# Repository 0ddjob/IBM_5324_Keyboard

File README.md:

# IBM System/23 Model 5324 Keyboard
Recreation of the keyboard for this computer to bring those without keyboards back to life.

## [Design References](/Design_Reference)

|     |Column A|Column B|Column C|Column D|Column E|Column F|Column G|Column H|Column I|Column J|Column K|
|-----|--------|--------|--------|--------|--------|--------|--------|--------|--------|--------|--------|
|Row 1| 6F/7F  | 3E     | 32     | 34     | 36     | 38     | 3A     | 3C     |        | 4B     |        |
|Row 2| 7C     | 31     | 33     | 35     | 37     |        | 39     | 3B     | 3D T   | 48     | 4C     |
|Row 3| 6D     | 20     | 22     | 24     | 26     |        | 28     | 2A     | 2C     | 47     | 49     |
|Row 4| 6C     | 54/74  | 21     | 23     | 25     | 27     | 29     | 2B     | 2D     | 44     | 4E     |
|Row 5| 6E     | 57/77  | 11     | 13     | 15     | 17     | 19     | 1B     | 59/79  | 45     | 46     |
|Row 6| 7D     | 70 T   | 12     | 14     | 16     |        | 18     | 1A     | 56/76  | 41     | 43     |
|Row 7| 71 T   | 73 T   | 0E     | 03     | 05     | 06     | 07     | 09     | 0B/7B  | 42     | 4D     |
|Row 8| 72 T   | 7E/5E  | 01     | 02     | 04     | 0F T   | 08     | 0A     | 68/78  | 40     | 4A     |

xx/yy = make/break key (send on release)<br>
T = typamatic key (repeat while held)<br>

## Keyboard Data Flow 
Refer p3-19 of the [SY34-0241-1 service manual.](/Datasheets/SY34-0241-1_IBM_5324_Computer_Service_Manual_May82_Keyboard.pdf)

The original keyboard uses a capacitive matrix where there is a capacitor for each key. When a key is pressed the capacitance increases.<br>

In my design we use standard key switches.<br>

The keyboard MCU has 11 drive lines to repeatedly scan the matrix - in my schematic these are the columns.<br>  

The increased capacitance of the active key's capacitor permits the drive-line (column) scan pulse to appear at one of the eight input lines to the sense amplifier - in my schematic these are the rows.<br>

The MCU uses the combination of the active drive line (column) and sense amplifier input line (row) to determine a scan code character (88 possible, 83 actually used).<br>

In my design the columns and rows are pulled high.  To scan the keyboard matrix we take each column low in turn.  A key press is detected when the key switch shorts the row to the column, taking the row low which is detected by the controller.  The combination of column and row is translated to a 5324 scan code and put on the bus via a buffer to ensure the 5324 accurately reads the code.<br>

An interrupt request is sent to the Model 5324 processing unit which will then read the scan code character.<br>

## Key Caps
[Key cap layout](https://gist.github.com/0ddjob/6a0642893fc0fdca74740a1e6c51e858)

|Size |Count|
|-----|-----|
|1u   |68   |
|1.25u|2    |
|1.5u |2    |
|1.75u|2    |
|2u   |6    |
|2.25u|1    |
|3u   |1    |
|9.5u |1    |
|TOTAL|83   |

|Size|Key|
|-----|---|
|1.25u|Backslash|
|1.25u|Shift LH|
|1.5u|Shift RH|
|1.5u|Field Advance|
|1.75u|Backspace|
|1.75u|Shift Lock|
|2u|Field Exit|
|2u|NP +|
|2u|NP -|
|2u|NP 0|
|2u|NP .|
|2u|Alt|
|2u|Enter (vertical)|
|3u|Field + (vertical)|
|9.5u|Space|

## [KiCad Design](/KiCad)
[Schematic](/IBM_5324_Keyboard_Schematic.pdf)

## [N-Key Rollover (NKRO) Design](/KiCad_NKRO)
Adding diodes to each key switch on their row connection.  The original keyboard doesn't have these so the modified behaviour might not be expected, thus it's "experimental".

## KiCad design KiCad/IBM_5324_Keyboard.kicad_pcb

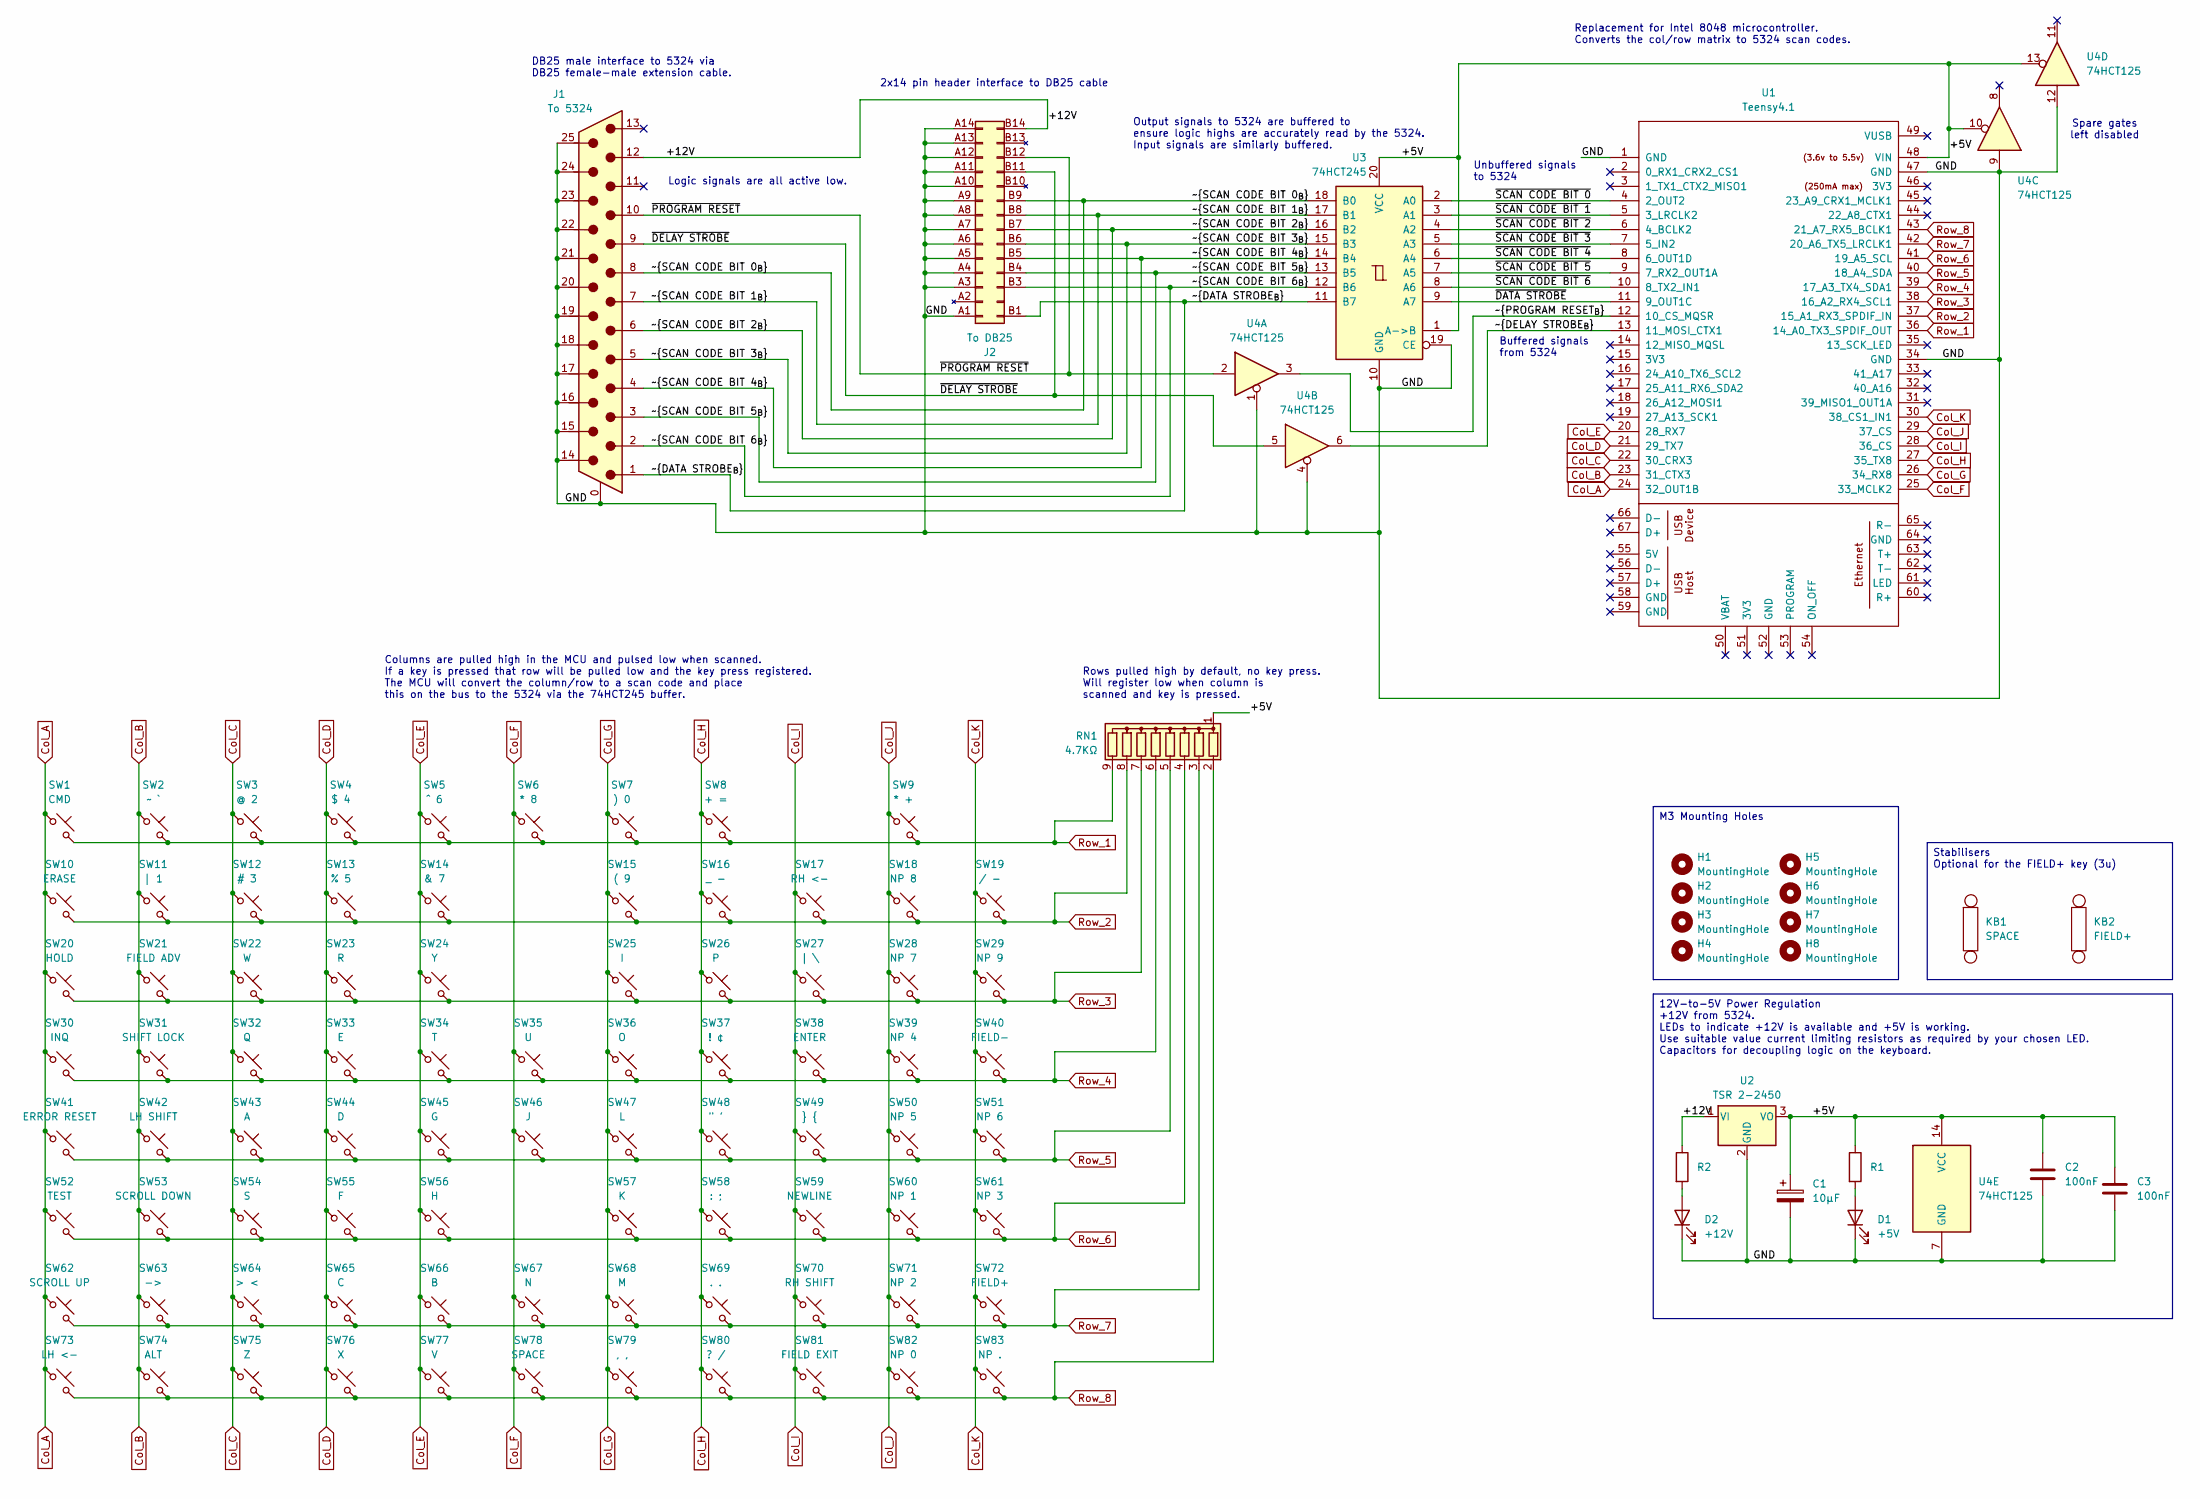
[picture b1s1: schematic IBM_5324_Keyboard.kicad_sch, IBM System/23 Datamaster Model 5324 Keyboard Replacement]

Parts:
C1: 10µF; CP_Radial_D5.0mm_P2.50mm
C2, C3: 100nF; C_Disc_D3.8mm_W2.6mm_P2.50mm
D1: +5V; LED_D5.0mm
D2: +12V; LED_D5.0mm
H1, H2, H3, H4, H5, H6, H7, H8: MountingHole; MountingHole_3.2mm_M3
J1: To 5324; L717SDB25P1ACH3R
J2: To DB25; PinHeader_2x14_P2.54mm_Vertical
KB1: SPACE; Stabilizer_Cherry_MX_8.00u
KB2: FIELD+; Stabilizer_Cherry_MX_3.00u
R1, R2: R; R_Axial_DIN0207_L6.3mm_D2.5mm_P7.62mm_Horizontal
RN1: 4.7KΩ; R_Array_SIP9
SW1: CMD; SW_Cherry_MX_PCB
SW2: ~ `; SW_Cherry_MX_PCB
SW3: @ 2; SW_Cherry_MX_PCB
SW4: $ 4; SW_Cherry_MX_PCB
SW5: ^ 6; SW_Cherry_MX_PCB
SW6: * 8; SW_Cherry_MX_PCB
SW7: ) 0; SW_Cherry_MX_PCB
SW8: + =; SW_Cherry_MX_PCB
SW9: * +; SW_Cherry_MX_PCB_1.75u
SW10: ERASE; SW_Cherry_MX_PCB
SW11: | 1; SW_Cherry_MX_PCB
SW12: # 3; SW_Cherry_MX_PCB
SW13: % 5; SW_Cherry_MX_PCB
SW14: & 7; SW_Cherry_MX_PCB
SW15: ( 9; SW_Cherry_MX_PCB
SW16: _ -; SW_Cherry_MX_PCB
SW17: RH <-; SW_Cherry_MX_PCB
SW18: NP 8; SW_Cherry_MX_PCB
SW19: / -; SW_Cherry_MX_PCB_1.75u
SW20: HOLD; SW_Cherry_MX_PCB
SW21: FIELD ADV; SW_Cherry_MX_PCB_1.50u
SW22: W; SW_Cherry_MX_PCB
SW23: R; SW_Cherry_MX_PCB
SW24: Y; SW_Cherry_MX_PCB
SW25: I; SW_Cherry_MX_PCB
SW26: P; SW_Cherry_MX_PCB
SW27: | \; SW_Cherry_MX_PCB
SW28: NP 7; SW_Cherry_MX_PCB
SW29: NP 9; SW_Cherry_MX_PCB
SW30: INQ; SW_Cherry_MX_PCB
SW31: SHIFT LOCK; SW_Cherry_MX_PCB_1.75u
SW32: Q; SW_Cherry_MX_PCB
SW33: E; SW_Cherry_MX_PCB
SW34: T; SW_Cherry_MX_PCB
SW35: U; SW_Cherry_MX_PCB
SW36: O; SW_Cherry_MX_PCB
SW37: ! ¢; SW_Cherry_MX_PCB
SW38: ENTER; SW_Cherry_MX_PCB_2.00u_90deg
SW39: NP 4; SW_Cherry_MX_PCB
SW40: FIELD-; SW_Cherry_MX_PCB
SW41: ERROR RESET; SW_Cherry_MX_PCB
SW42: LH SHIFT; SW_Cherry_MX_PCB_1.25u
SW43: A; SW_Cherry_MX_PCB
SW44: D; SW_Cherry_MX_PCB
SW45: G; SW_Cherry_MX_PCB
SW46: J; SW_Cherry_MX_PCB
SW47: L; SW_Cherry_MX_PCB
SW48: " '; SW_Cherry_MX_PCB
SW49: } {; SW_Cherry_MX_PCB
SW50: NP 5; SW_Cherry_MX_PCB
SW51: NP 6; SW_Cherry_MX_PCB
SW52: TEST; SW_Cherry_MX_PCB
SW53: SCROLL DOWN; SW_Cherry_MX_PCB
SW54: S; SW_Cherry_MX_PCB
SW55: F; SW_Cherry_MX_PCB
SW56: H; SW_Cherry_MX_PCB
SW57: K; SW_Cherry_MX_PCB
SW58: : ;; SW_Cherry_MX_PCB
SW59: NEWLINE; SW_Cherry_MX_PCB
SW60: NP 1; SW_Cherry_MX_PCB
SW61: NP 3; SW_Cherry_MX_PCB
SW62: SCROLL UP; SW_Cherry_MX_PCB
SW63: ->; SW_Cherry_MX_PCB
SW64: > <; SW_Cherry_MX_PCB_1.00u
SW65: C; SW_Cherry_MX_PCB
SW66: B; SW_Cherry_MX_PCB
SW67: N; SW_Cherry_MX_PCB
SW68: M; SW_Cherry_MX_PCB
SW69: . .; SW_Cherry_MX_PCB
SW70: RH SHIFT; SW_Cherry_MX_PCB_1.50u
SW71: NP 2; SW_Cherry_MX_PCB
SW72: FIELD+; SW_Cherry_MX_PCB_3.00u_90deg
SW73: LH <-; SW_Cherry_MX_PCB
SW74: ALT; SW_Cherry_MX_PCB_2.25u
SW75: Z; SW_Cherry_MX_PCB
SW76: X; SW_Cherry_MX_PCB
SW77: V; SW_Cherry_MX_PCB
SW78: SPACE; SW_Cherry_MX_PCB
SW79: , ,; SW_Cherry_MX_PCB
SW80: ? /; SW_Cherry_MX_PCB
SW81: FIELD EXIT; SW_Cherry_MX_PCB_2.00u
SW82: NP 0; SW_Cherry_MX_PCB_2.00u
SW83: NP .; SW_Cherry_MX_PCB_2.00u
U1: Teensy4.1; Teensy41
U2: TSR 2-2450; Converter_DCDC_TRACO_TSR2-24xxN_TSR2-24xxxN_THT
U3: 74HCT245; DIP-20_W7.62mm
U4: 74HCT125; DIP-14_W7.62mm

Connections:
/+5V: C1.1, C2.1, C3.1, R1.1, RN1.1 (common), U1.48 (VIN), U2.3 (VO), U3.1 (A->B), U3.20 (VCC), U4.10, U4.13, U4.14 (VCC)
/+12V: J1.12, J2.B14 (+12V), R2.1, U2.1 (VI)
/GND: C1.2, C2.2, C3.2, D1.1 (K), D2.1 (K), J1.0 (PAD), J1.14, J1.15, J1.16, J1.17, J1.18, J1.19, J1.20, J1.21, J1.22, J1.23, J1.24, J1.25, J2.A1 (GND), J2.A3 (GND), J2.A4 (GND), J2.A5 (GND), J2.A6 (GND), J2.A7 (GND), J2.A8 (GND), J2.A9 (GND), J2.A10 (GND), J2.A11 (GND), J2.A12 (GND), J2.A13 (GND), J2.A14 (GND), U1.1 (GND), U1.34 (GND), U1.47 (GND), U2.2 (GND), U3.10 (GND), U3.19 (CE), U4.1, U4.4, U4.7 (GND), U4.9, U4.12
/~DATA STROBE_{B}: J1.1, J2.B1 (DATA_STROBE), U3.11 (B7)
/~DATA STROBE: U1.11 (9_OUT1C), U3.9 (A7)
/~DELAY STROBE_{B}: U1.13 (11_MOSI_CTX1), U4.6
/~DELAY STROBE: J1.9, J2.B11 (DELAY_STROBE), U4.5
/~PROGRAM RESET_{B}: U1.12 (10_CS_MQSR), U4.3
/~PROGRAM RESET: J1.10, J2.B12 (PROGRAM_RESET), U4.2
/~SCAN CODE BIT 0_{B}: J1.8, J2.B9 (SCAN_CODE_BIT_0), U3.18 (B0)
/~SCAN CODE BIT 0: U1.4 (2_OUT2), U3.2 (A0)
/~SCAN CODE BIT 1_{B}: J1.7, J2.B8 (SCAN_CODE_BIT_1), U3.17 (B1)
/~SCAN CODE BIT 1: U1.5 (3_LRCLK2), U3.3 (A1)
/~SCAN CODE BIT 2_{B}: J1.6, J2.B7 (SCAN_CODE_BIT_2), U3.16 (B2)
/~SCAN CODE BIT 2: U1.6 (4_BCLK2), U3.4 (A2)
/~SCAN CODE BIT 3_{B}: J1.5, J2.B6 (SCAN_CODE_BIT_3), U3.15 (B3)
/~SCAN CODE BIT 3: U1.7 (5_IN2), U3.5 (A3)
/~SCAN CODE BIT 4_{B}: J1.4, J2.B5 (SCAN_CODE_BIT_4), U3.14 (B4)
/~SCAN CODE BIT 4: U1.8 (6_OUT1D), U3.6 (A4)
/~SCAN CODE BIT 5_{B}: J1.3, J2.B4 (SCAN_CODE_BIT_5), U3.13 (B5)
/~SCAN CODE BIT 5: U1.9 (7_RX2_OUT1A), U3.7 (A5)
/~SCAN CODE BIT 6_{B}: J1.2, J2.B3 (SCAN_CODE_BIT_6), U3.12 (B6)
/~SCAN CODE BIT 6: U1.10 (8_TX2_IN1), U3.8 (A6)
Col_A: SW1.1, SW10.1, SW20.1, SW30.1, SW41.1, SW52.1, SW62.1, SW73.1, U1.24 (32_OUT1B)
Col_B: SW2.1, SW11.1, SW21.1, SW31.1, SW42.1, SW53.1, SW63.1, SW74.1, U1.23 (31_CTX3)
Col_C: SW3.1, SW12.1, SW22.1, SW32.1, SW43.1, SW54.1, SW64.1, SW75.1, U1.22 (30_CRX3)
Col_D: SW4.1, SW13.1, SW23.1, SW33.1, SW44.1, SW55.1, SW65.1, SW76.1, U1.21 (29_TX7)
Col_E: SW5.1, SW14.1, SW24.1, SW34.1, SW45.1, SW56.1, SW66.1, SW77.1, U1.20 (28_RX7)
Col_F: SW6.1, SW35.1, SW46.1, SW67.1, SW78.1, U1.25 (33_MCLK2)
Col_G: SW7.1, SW15.1, SW25.1, SW36.1, SW47.1, SW57.1, SW68.1, SW79.1, U1.26 (34_RX8)
Col_H: SW8.1, SW16.1, SW26.1, SW37.1, SW48.1, SW58.1, SW69.1, SW80.1, U1.27 (35_TX8)
Col_I: SW17.1, SW27.1, SW38.1, SW49.1, SW59.1, SW70.1, SW81.1, U1.28 (36_CS)
Col_J: SW9.1, SW18.1, SW28.1, SW39.1, SW50.1, SW60.1, SW71.1, SW82.1, U1.29 (37_CS)
Col_K: SW19.1, SW29.1, SW40.1, SW51.1, SW61.1, SW72.1, SW83.1, U1.30 (38_CS1_IN1)
unnamed: D1.2 (A), R1.2
unnamed: D2.2 (A), R2.2
Row_1: RN1.9 (R8), SW1.2, SW2.2, SW3.2, SW4.2, SW5.2, SW6.2, SW7.2, SW8.2, SW9.2, U1.36 (14_A0_TX3_SPDIF_OUT)
Row_2: RN1.8 (R7), SW10.2, SW11.2, SW12.2, SW13.2, SW14.2, SW15.2, SW16.2, SW17.2, SW18.2, SW19.2, U1.37 (15_A1_RX3_SPDIF_IN)
Row_3: RN1.7 (R6), SW20.2, SW21.2, SW22.2, SW23.2, SW24.2, SW25.2, SW26.2, SW27.2, SW28.2, SW29.2, U1.38 (16_A2_RX4_SCL1)
Row_4: RN1.6 (R5), SW30.2, SW31.2, SW32.2, SW33.2, SW34.2, SW35.2, SW36.2, SW37.2, SW38.2, SW39.2, SW40.2, U1.39 (17_A3_TX4_SDA1)
Row_5: RN1.5 (R4), SW41.2, SW42.2, SW43.2, SW44.2, SW45.2, SW46.2, SW47.2, SW48.2, SW49.2, SW50.2, SW51.2, U1.40 (18_A4_SDA)
Row_6: RN1.4 (R3), SW52.2, SW53.2, SW54.2, SW55.2, SW56.2, SW57.2, SW58.2, SW59.2, SW60.2, SW61.2, U1.41 (19_A5_SCL)
Row_7: RN1.3 (R2), SW62.2, SW63.2, SW64.2, SW65.2, SW66.2, SW67.2, SW68.2, SW69.2, SW70.2, SW71.2, SW72.2, U1.42 (20_A6_TX5_LRCLK1)
Row_8: RN1.2 (R1), SW73.2, SW74.2, SW75.2, SW76.2, SW77.2, SW78.2, SW79.2, SW80.2, SW81.2, SW82.2, SW83.2, U1.43 (21_A7_RX5_BCLK1)

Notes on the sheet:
Columns are pulled high in the MCU and pulsed low when scanned. If a key is pressed that row will be pulled low and the key press registered. The MCU will convert the column/row to a scan code and place this on the bus to the 5324 via the 74HCT245 buffer.
Buffered signals from 5324
Spare gates left disabled
Logic signals are all active low.
2x14 pin header interface to DB25 cable
Replacement for Intel 8048 microcontroller. Converts the col/row matrix to 5324 scan codes.
DB25 male interface to 5324 via DB25 female-male extension cable.
Unbuffered signals to 5324
Output signals to 5324 are buffered to ensure logic highs are accurately read by the 5324. Input signals are similarly buffered.
Rows pulled high by default, no key press. Will register low when column is scanned and key is pressed.
M3 Mounting Holes
Stabilisers Optional for the FIELD+ key (3u)
12V-to-5V Power Regulation +12V from 5324. LEDs to indicate +12V is available and +5V is working. Use suitable value current limiting resistors as required by your chosen LED. Capacitors for decoupling logic on the keyboard.

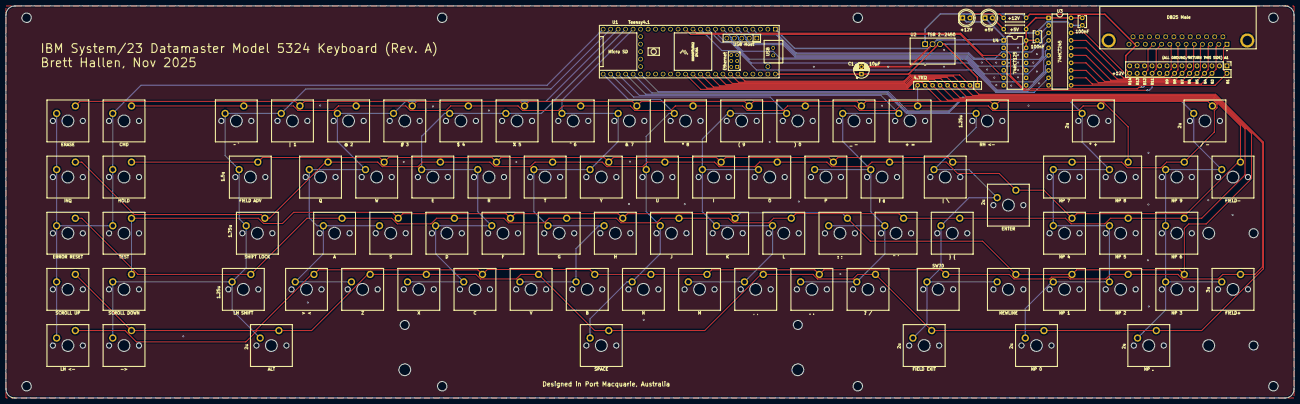
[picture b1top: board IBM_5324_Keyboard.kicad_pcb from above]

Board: 2 copper layers, 437.0 x 133.0 mm, 107 parts (0 on the bottom side), 44 nets.

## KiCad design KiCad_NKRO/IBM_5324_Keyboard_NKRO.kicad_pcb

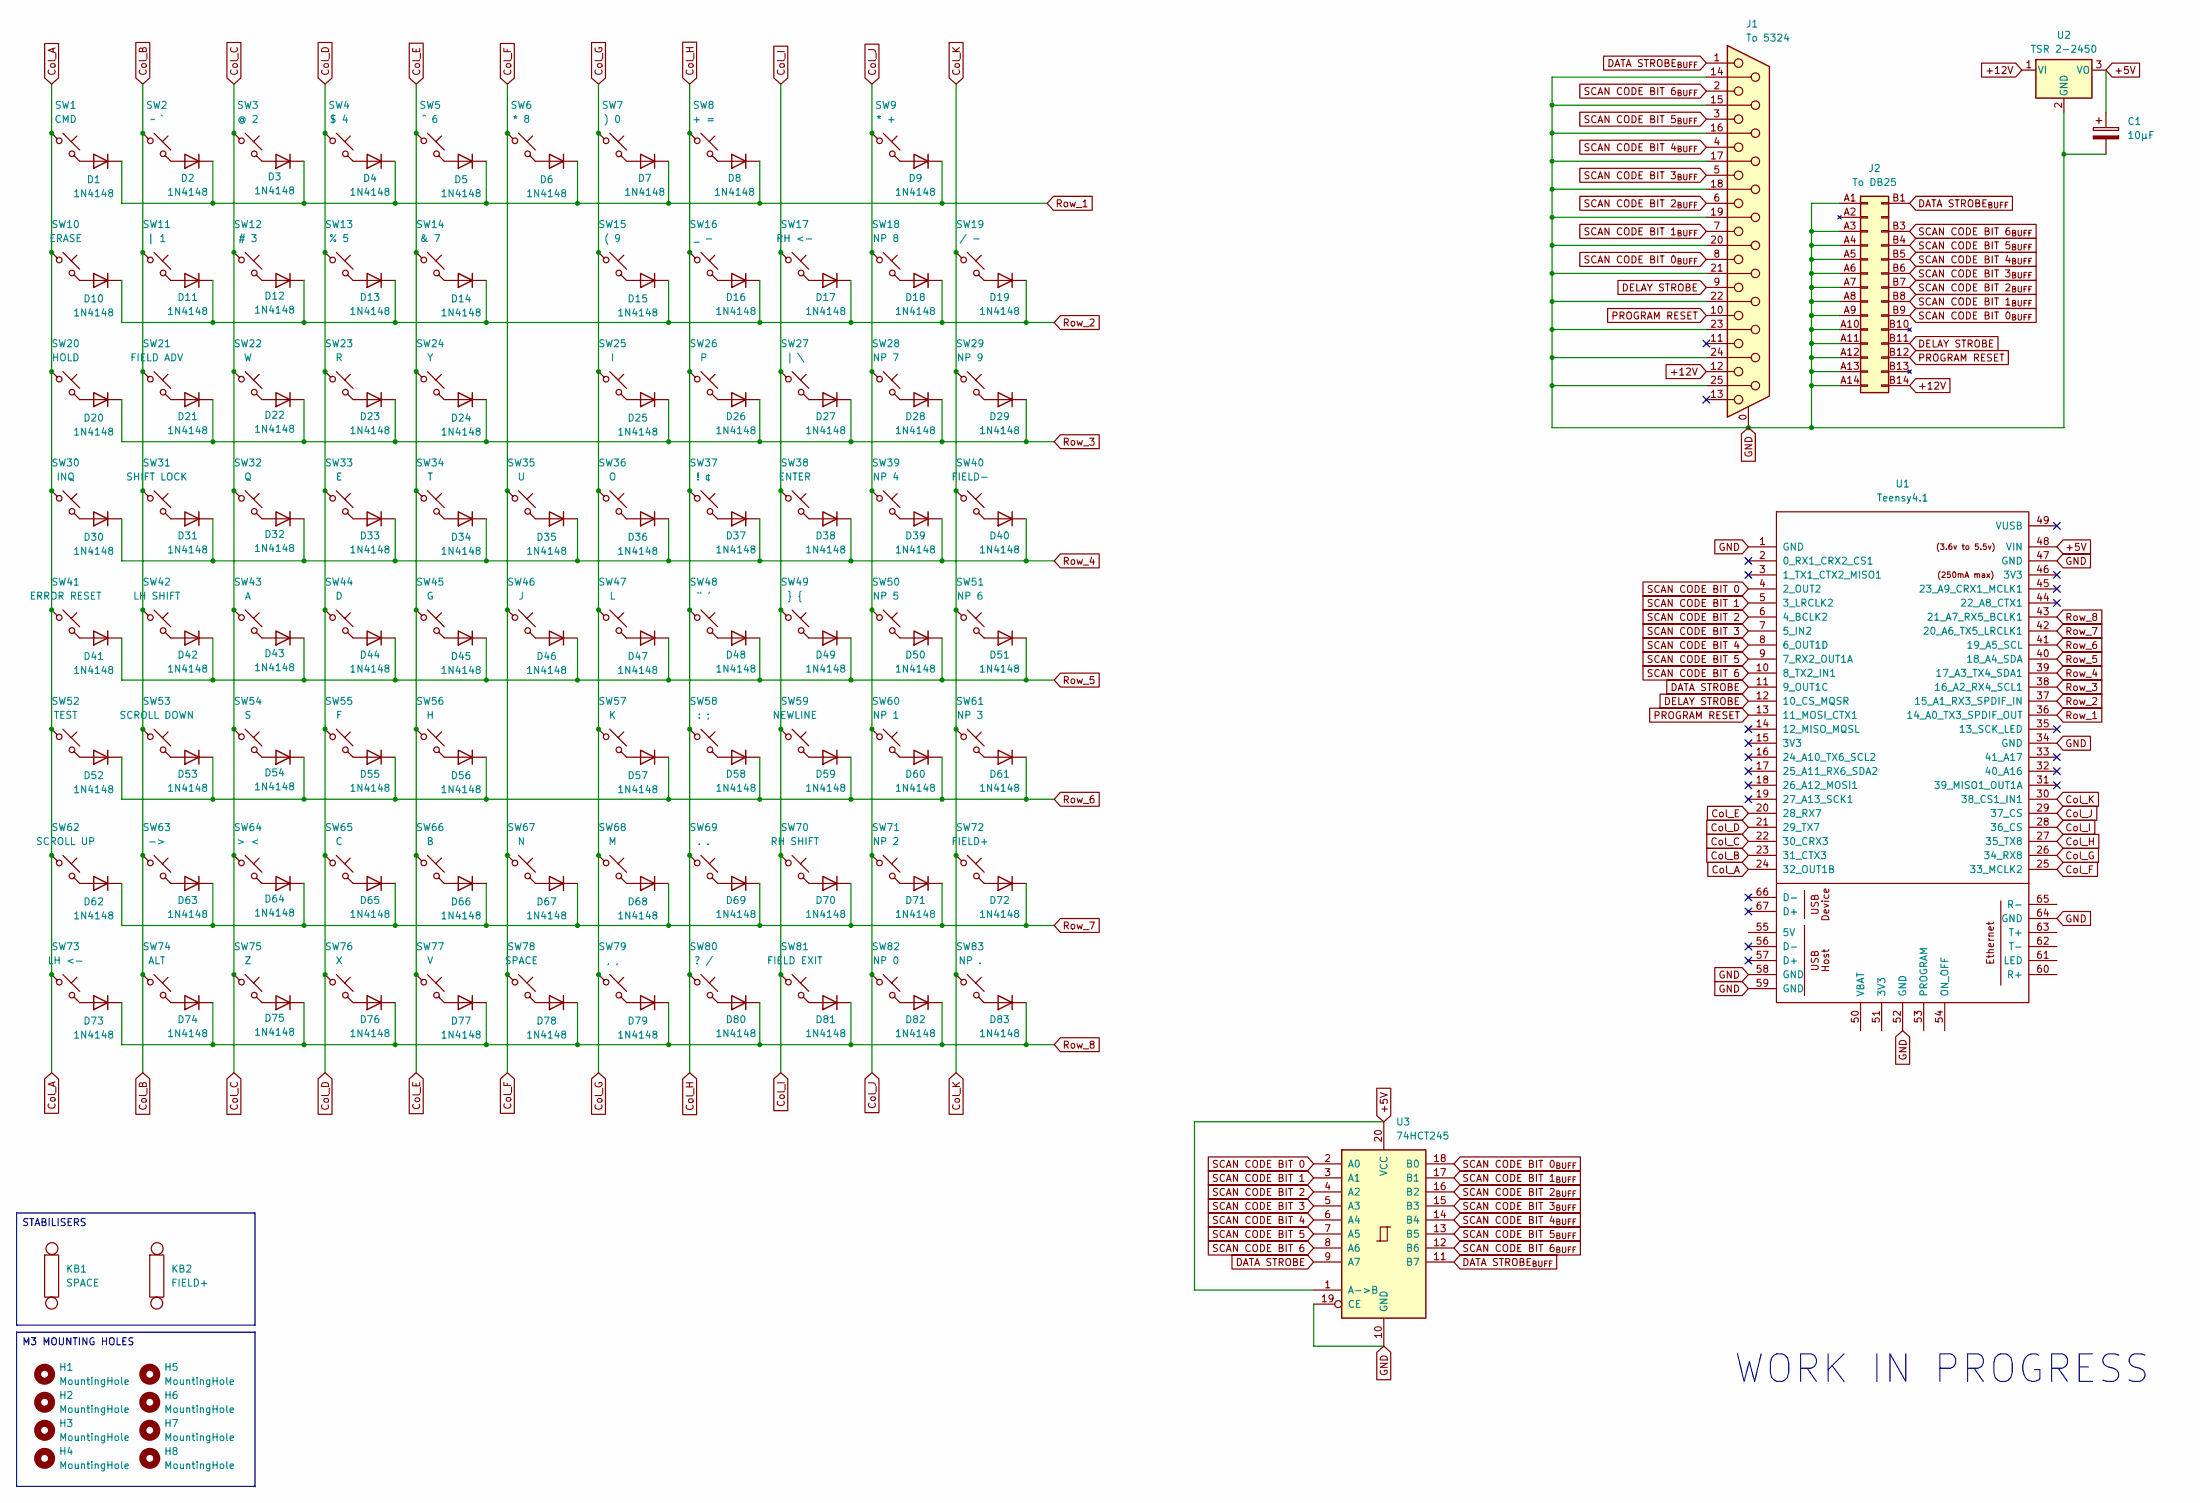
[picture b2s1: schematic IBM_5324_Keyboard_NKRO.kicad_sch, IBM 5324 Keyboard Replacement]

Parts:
C1: 10µF; CP_Radial_D5.0mm_P2.50mm
D1, D2, D3, D4, D5, D6, D7, D8, D9, D10, D11, D12, D13, D14, D15, D16, D17, D18, D19, D20, D21, D22, D23, D24, D25, D26, D27, D28, D29, D30, D31, D32, D33, D34, D35, D36, D37, D38, D39, D40, D41, D42, D43, D44, D45, D46, D47, D48, D49, D50, D51, D52, D53, D54, D55, D56, D57, D58, D59, D60, D61, D62, D63, D64, D65, D66, D67, D68, D69, D70, D71, D72, D73, D74, D75, D76, D77, D78, D79, D80, D81, D82, D83: 1N4148; D_SOD-123
H1, H2, H3, H4, H5, H6, H7, H8: MountingHole; MountingHole_3.2mm_M3
J1: To 5324; L77SDB25SA4CH4F
J2: To DB25; PinHeader_2x14_P2.54mm_Vertical
KB1: SPACE; Stabilizer_Cherry_MX_8.00u
KB2: FIELD+; Stabilizer_Cherry_MX_3.00u
SW1: CMD; SW_Cherry_MX_PCB
SW2: ~ `; SW_Cherry_MX_PCB
SW3: @ 2; SW_Cherry_MX_PCB
SW4: $ 4; SW_Cherry_MX_PCB
SW5: ^ 6; SW_Cherry_MX_PCB
SW6: * 8; SW_Cherry_MX_PCB
SW7: ) 0; SW_Cherry_MX_PCB
SW8: + =; SW_Cherry_MX_PCB
SW9: * +; SW_Cherry_MX_PCB_1.75u
SW10: ERASE; SW_Cherry_MX_PCB
SW11: | 1; SW_Cherry_MX_PCB
SW12: # 3; SW_Cherry_MX_PCB
SW13: % 5; SW_Cherry_MX_PCB
SW14: & 7; SW_Cherry_MX_PCB
SW15: ( 9; SW_Cherry_MX_PCB
SW16: _ -; SW_Cherry_MX_PCB
SW17: RH <-; SW_Cherry_MX_PCB
SW18: NP 8; SW_Cherry_MX_PCB
SW19: / -; SW_Cherry_MX_PCB_1.75u
SW20: HOLD; SW_Cherry_MX_PCB
SW21: FIELD ADV; SW_Cherry_MX_PCB_1.50u
SW22: W; SW_Cherry_MX_PCB
SW23: R; SW_Cherry_MX_PCB
SW24: Y; SW_Cherry_MX_PCB
SW25: I; SW_Cherry_MX_PCB
SW26: P; SW_Cherry_MX_PCB
SW27: | \; SW_Cherry_MX_PCB
SW28: NP 7; SW_Cherry_MX_PCB
SW29: NP 9; SW_Cherry_MX_PCB
SW30: INQ; SW_Cherry_MX_PCB
SW31: SHIFT LOCK; SW_Cherry_MX_PCB_1.75u
SW32: Q; SW_Cherry_MX_PCB
SW33: E; SW_Cherry_MX_PCB
SW34: T; SW_Cherry_MX_PCB
SW35: U; SW_Cherry_MX_PCB
SW36: O; SW_Cherry_MX_PCB
SW37: ! ¢; SW_Cherry_MX_PCB
SW38: ENTER; SW_Cherry_MX_PCB_2.00u_90deg
SW39: NP 4; SW_Cherry_MX_PCB
SW40: FIELD-; SW_Cherry_MX_PCB
SW41: ERROR RESET; SW_Cherry_MX_PCB
SW42: LH SHIFT; SW_Cherry_MX_PCB_1.25u
SW43: A; SW_Cherry_MX_PCB
SW44: D; SW_Cherry_MX_PCB
SW45: G; SW_Cherry_MX_PCB
SW46: J; SW_Cherry_MX_PCB
SW47: L; SW_Cherry_MX_PCB
SW48: " '; SW_Cherry_MX_PCB
SW49: } {; SW_Cherry_MX_PCB
SW50: NP 5; SW_Cherry_MX_PCB
SW51: NP 6; SW_Cherry_MX_PCB
SW52: TEST; SW_Cherry_MX_PCB
SW53: SCROLL DOWN; SW_Cherry_MX_PCB
SW54: S; SW_Cherry_MX_PCB
SW55: F; SW_Cherry_MX_PCB
SW56: H; SW_Cherry_MX_PCB
SW57: K; SW_Cherry_MX_PCB
SW58: : ;; SW_Cherry_MX_PCB
SW59: NEWLINE; SW_Cherry_MX_PCB
SW60: NP 1; SW_Cherry_MX_PCB
SW61: NP 3; SW_Cherry_MX_PCB
SW62: SCROLL UP; SW_Cherry_MX_PCB
SW63: ->; SW_Cherry_MX_PCB
SW64: > <; SW_Cherry_MX_PCB_1.00u
SW65: C; SW_Cherry_MX_PCB
SW66: B; SW_Cherry_MX_PCB
SW67: N; SW_Cherry_MX_PCB
SW68: M; SW_Cherry_MX_PCB
SW69: . .; SW_Cherry_MX_PCB
SW70: RH SHIFT; SW_Cherry_MX_PCB_1.50u
SW71: NP 2; SW_Cherry_MX_PCB
SW72: FIELD+; SW_Cherry_MX_PCB_3.00u_90deg
SW73: LH <-; SW_Cherry_MX_PCB
SW74: ALT; SW_Cherry_MX_PCB_2.25u
SW75: Z; SW_Cherry_MX_PCB
SW76: X; SW_Cherry_MX_PCB
SW77: V; SW_Cherry_MX_PCB
SW78: SPACE; SW_Cherry_MX_PCB
SW79: , ,; SW_Cherry_MX_PCB
SW80: ? /; SW_Cherry_MX_PCB
SW81: FIELD EXIT; SW_Cherry_MX_PCB_2.00u
SW82: NP 0; SW_Cherry_MX_PCB_2.00u
SW83: NP .; SW_Cherry_MX_PCB_2.00u
U1: Teensy4.1; Teensy41
U2: TSR 2-2450; Converter_DCDC_TRACO_TSR2-24xxN_TSR2-24xxxN_THT
U3: 74HCT245; DIP-18_W7.62mm

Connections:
+5V: C1.1, U1.48 (VIN), U2.3 (VO), U3.1 (A->B), U3.20 (VCC)
+12V: J1.12, J2.B14 (+12V), U2.1 (VI)
Col_A: SW1.1, SW10.1, SW20.1, SW30.1, SW41.1, SW52.1, SW62.1, SW73.1, U1.24 (32_OUT1B)
Col_B: SW2.1, SW11.1, SW21.1, SW31.1, SW42.1, SW53.1, SW63.1, SW74.1, U1.23 (31_CTX3)
Col_C: SW3.1, SW12.1, SW22.1, SW32.1, SW43.1, SW54.1, SW64.1, SW75.1, U1.22 (30_CRX3)
Col_D: SW4.1, SW13.1, SW23.1, SW33.1, SW44.1, SW55.1, SW65.1, SW76.1, U1.21 (29_TX7)
Col_E: SW5.1, SW14.1, SW24.1, SW34.1, SW45.1, SW56.1, SW66.1, SW77.1, U1.20 (28_RX7)
Col_F: SW6.1, SW35.1, SW46.1, SW67.1, SW78.1, U1.25 (33_MCLK2)
Col_G: SW7.1, SW15.1, SW25.1, SW36.1, SW47.1, SW57.1, SW68.1, SW79.1, U1.26 (34_RX8)
Col_H: SW8.1, SW16.1, SW26.1, SW37.1, SW48.1, SW58.1, SW69.1, SW80.1, U1.27 (35_TX8)
Col_I: SW17.1, SW27.1, SW38.1, SW49.1, SW59.1, SW70.1, SW81.1, U1.28 (36_CS)
Col_J: SW9.1, SW18.1, SW28.1, SW39.1, SW50.1, SW60.1, SW71.1, SW82.1, U1.29 (37_CS)
Col_K: SW19.1, SW29.1, SW40.1, SW51.1, SW61.1, SW72.1, SW83.1, U1.30 (38_CS1_IN1)
DATA STROBE: U1.11 (9_OUT1C), U3.9 (A7)
DATA STROBE_{BUFF}: J1.1, J2.B1 (DATA_STROBE), U3.11 (B7)
DELAY STROBE: J1.9, J2.B11 (DELAY_STROBE), U1.12 (10_CS_MQSR)
GND: C1.2, J1.0 (PAD), J1.14, J1.15, J1.16, J1.17, J1.18, J1.19, J1.20, J1.21, J1.22, J1.23, J1.24, J1.25, J2.A1 (GND), J2.A3 (GND), J2.A4 (GND), J2.A5 (GND), J2.A6 (GND), J2.A7 (GND), J2.A8 (GND), J2.A9 (GND), J2.A10 (GND), J2.A11 (GND), J2.A12 (GND), J2.A13 (GND), J2.A14 (GND), U1.1 (GND), U1.34 (GND), U1.47 (GND), U1.52 (GND), U1.58 (GND), U1.59 (GND), U1.64 (GND), U2.2 (GND), U3.10 (GND), U3.19 (CE)
unnamed: D1.2 (A), SW1.2
unnamed: D2.2 (A), SW2.2
unnamed: D3.2 (A), SW3.2
unnamed: D4.2 (A), SW4.2
unnamed: D5.2 (A), SW5.2
unnamed: D6.2 (A), SW6.2
unnamed: D7.2 (A), SW7.2
unnamed: D8.2 (A), SW8.2
unnamed: D9.2 (A), SW9.2
unnamed: D10.2 (A), SW10.2
unnamed: D11.2 (A), SW11.2
unnamed: D12.2 (A), SW12.2
unnamed: D13.2 (A), SW13.2
unnamed: D14.2 (A), SW14.2
unnamed: D15.2 (A), SW15.2
unnamed: D16.2 (A), SW16.2
unnamed: D17.2 (A), SW17.2
unnamed: D18.2 (A), SW18.2
unnamed: D19.2 (A), SW19.2
unnamed: D20.2 (A), SW20.2
unnamed: D21.2 (A), SW21.2
unnamed: D22.2 (A), SW22.2
unnamed: D23.2 (A), SW23.2
unnamed: D24.2 (A), SW24.2
unnamed: D25.2 (A), SW25.2
unnamed: D26.2 (A), SW26.2
unnamed: D27.2 (A), SW27.2
unnamed: D28.2 (A), SW28.2
unnamed: D29.2 (A), SW29.2
unnamed: D30.2 (A), SW30.2
unnamed: D31.2 (A), SW31.2
unnamed: D32.2 (A), SW32.2
unnamed: D33.2 (A), SW33.2
unnamed: D34.2 (A), SW34.2
unnamed: D35.2 (A), SW35.2
unnamed: D36.2 (A), SW36.2
unnamed: D37.2 (A), SW37.2
unnamed: D38.2 (A), SW38.2
unnamed: D39.2 (A), SW39.2
unnamed: D40.2 (A), SW40.2
unnamed: D41.2 (A), SW41.2
unnamed: D42.2 (A), SW42.2
unnamed: D43.2 (A), SW43.2
unnamed: D44.2 (A), SW44.2
unnamed: D45.2 (A), SW45.2
unnamed: D46.2 (A), SW46.2
unnamed: D47.2 (A), SW47.2
unnamed: D48.2 (A), SW48.2
unnamed: D49.2 (A), SW49.2
unnamed: D50.2 (A), SW50.2
unnamed: D51.2 (A), SW51.2
unnamed: D52.2 (A), SW52.2
unnamed: D53.2 (A), SW53.2
unnamed: D54.2 (A), SW54.2
unnamed: D55.2 (A), SW55.2
unnamed: D56.2 (A), SW56.2
unnamed: D57.2 (A), SW57.2
unnamed: D58.2 (A), SW58.2
unnamed: D59.2 (A), SW59.2
unnamed: D60.2 (A), SW60.2
unnamed: D61.2 (A), SW61.2
unnamed: D62.2 (A), SW62.2
unnamed: D63.2 (A), SW63.2
unnamed: D64.2 (A), SW64.2
unnamed: D65.2 (A), SW65.2
unnamed: D66.2 (A), SW66.2
unnamed: D67.2 (A), SW67.2
unnamed: D68.2 (A), SW68.2
unnamed: D69.2 (A), SW69.2
unnamed: D70.2 (A), SW70.2
unnamed: D71.2 (A), SW71.2
unnamed: D72.2 (A), SW72.2
unnamed: D73.2 (A), SW73.2
unnamed: D74.2 (A), SW74.2
unnamed: D75.2 (A), SW75.2
unnamed: D76.2 (A), SW76.2
unnamed: D77.2 (A), SW77.2
unnamed: D78.2 (A), SW78.2
unnamed: D79.2 (A), SW79.2
unnamed: D80.2 (A), SW80.2
unnamed: D81.2 (A), SW81.2
unnamed: D82.2 (A), SW82.2
unnamed: D83.2 (A), SW83.2
PROGRAM RESET: J1.10, J2.B12 (PROGRAM_RESET), U1.13 (11_MOSI_CTX1)
Row_1: D1.1 (K), D2.1 (K), D3.1 (K), D4.1 (K), D5.1 (K), D6.1 (K), D7.1 (K), D8.1 (K), D9.1 (K), U1.36 (14_A0_TX3_SPDIF_OUT)
Row_2: D10.1 (K), D11.1 (K), D12.1 (K), D13.1 (K), D14.1 (K), D15.1 (K), D16.1 (K), D17.1 (K), D18.1 (K), D19.1 (K), U1.37 (15_A1_RX3_SPDIF_IN)
Row_3: D20.1 (K), D21.1 (K), D22.1 (K), D23.1 (K), D24.1 (K), D25.1 (K), D26.1 (K), D27.1 (K), D28.1 (K), D29.1 (K), U1.38 (16_A2_RX4_SCL1)
Row_4: D30.1 (K), D31.1 (K), D32.1 (K), D33.1 (K), D34.1 (K), D35.1 (K), D36.1 (K), D37.1 (K), D38.1 (K), D39.1 (K), D40.1 (K), U1.39 (17_A3_TX4_SDA1)
Row_5: D41.1 (K), D42.1 (K), D43.1 (K), D44.1 (K), D45.1 (K), D46.1 (K), D47.1 (K), D48.1 (K), D49.1 (K), D50.1 (K), D51.1 (K), U1.40 (18_A4_SDA)
Row_6: D52.1 (K), D53.1 (K), D54.1 (K), D55.1 (K), D56.1 (K), D57.1 (K), D58.1 (K), D59.1 (K), D60.1 (K), D61.1 (K), U1.41 (19_A5_SCL)
Row_7: D62.1 (K), D63.1 (K), D64.1 (K), D65.1 (K), D66.1 (K), D67.1 (K), D68.1 (K), D69.1 (K), D70.1 (K), D71.1 (K), D72.1 (K), U1.42 (20_A6_TX5_LRCLK1)
Row_8: D73.1 (K), D74.1 (K), D75.1 (K), D76.1 (K), D77.1 (K), D78.1 (K), D79.1 (K), D80.1 (K), D81.1 (K), D82.1 (K), D83.1 (K), U1.43 (21_A7_RX5_BCLK1)
SCAN CODE BIT 0: U1.4 (2_OUT2), U3.2 (A0)
SCAN CODE BIT 0_{BUFF}: J1.8, J2.B9 (SCAN_CODE_BIT_0), U3.18 (B0)
SCAN CODE BIT 1: U1.5 (3_LRCLK2), U3.3 (A1)
SCAN CODE BIT 1_{BUFF}: J1.7, J2.B8 (SCAN_CODE_BIT_1), U3.17 (B1)
SCAN CODE BIT 2: U1.6 (4_BCLK2), U3.4 (A2)
SCAN CODE BIT 2_{BUFF}: J1.6, J2.B7 (SCAN_CODE_BIT_2), U3.16 (B2)
SCAN CODE BIT 3: U1.7 (5_IN2), U3.5 (A3)
SCAN CODE BIT 3_{BUFF}: J1.5, J2.B6 (SCAN_CODE_BIT_3), U3.15 (B3)
SCAN CODE BIT 4: U1.8 (6_OUT1D), U3.6 (A4)
SCAN CODE BIT 4_{BUFF}: J1.4, J2.B5 (SCAN_CODE_BIT_4), U3.14 (B4)
SCAN CODE BIT 5: U1.9 (7_RX2_OUT1A), U3.7 (A5)
SCAN CODE BIT 5_{BUFF}: J1.3, J2.B4 (SCAN_CODE_BIT_5), U3.13 (B5)
SCAN CODE BIT 6: U1.10 (8_TX2_IN1), U3.8 (A6)
SCAN CODE BIT 6_{BUFF}: J1.2, J2.B3 (SCAN_CODE_BIT_6), U3.12 (B6)

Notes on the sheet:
WORK IN PROGRESS
M3 MOUNTING HOLES
STABILISERS

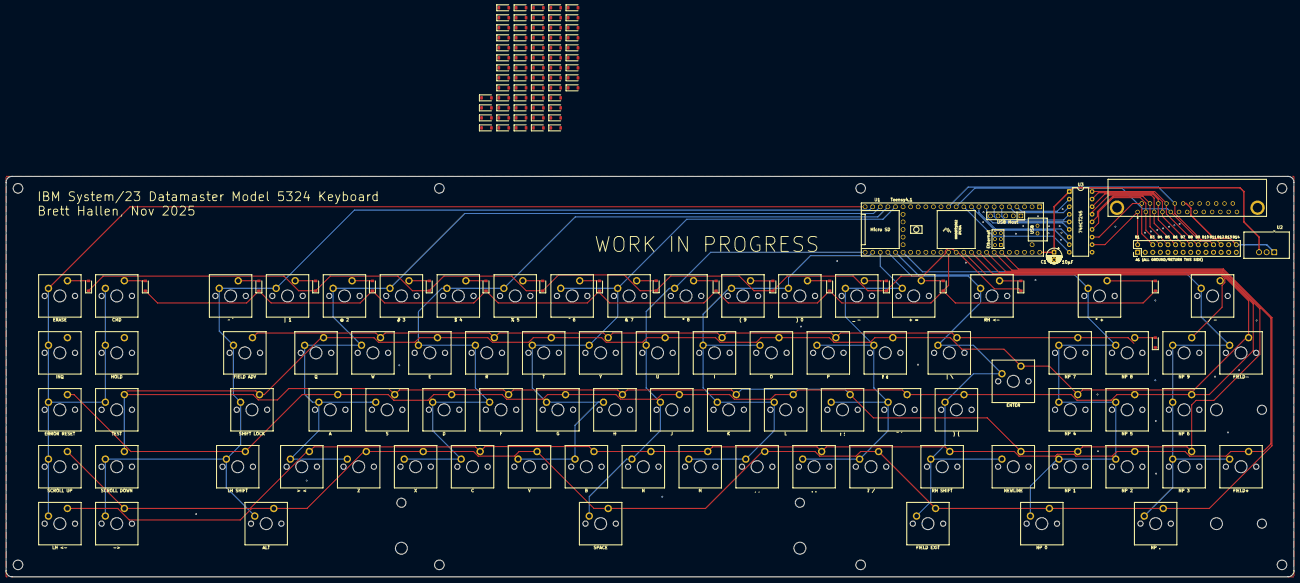
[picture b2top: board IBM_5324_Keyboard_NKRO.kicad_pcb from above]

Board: 2 copper layers, 431.0 x 134.0 mm, 182 parts (0 on the bottom side), 123 nets.

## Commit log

2025-11-26 Further work
2025-11-26 Updated keycap layout
2025-11-26 Layout updated
2025-11-27 Progressing design
2025-11-27 Key switch routing completed
2025-11-27 Started work on firmware
2025-11-27 Started firmware development
2025-11-27 Design tweaks
2025-11-28 Swapped DB25 female to male
2025-11-28 Added external pull-up array on rows
2025-11-28 Revised schematic & PCB layout
2025-11-29 Modified to indicate signals are active LOW
2025-11-29 Further refinements to PCB layout
    - missing value text on some parts
    - isolated ground on 74LS245
2025-11-30 Keyboard 8048 binary & disassembly
